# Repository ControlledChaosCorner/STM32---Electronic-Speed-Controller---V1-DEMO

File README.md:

# STM32---Electronic-Speed-Controller---V1-DEMO

The first version as a proof of concept and schematic verification for a simple brushed and brushless ESC. Based around an STM32, this will be an open source project starting point that will soon be replaced by a fully self contained, fully functional ESC. Files Designed for use in KiCad

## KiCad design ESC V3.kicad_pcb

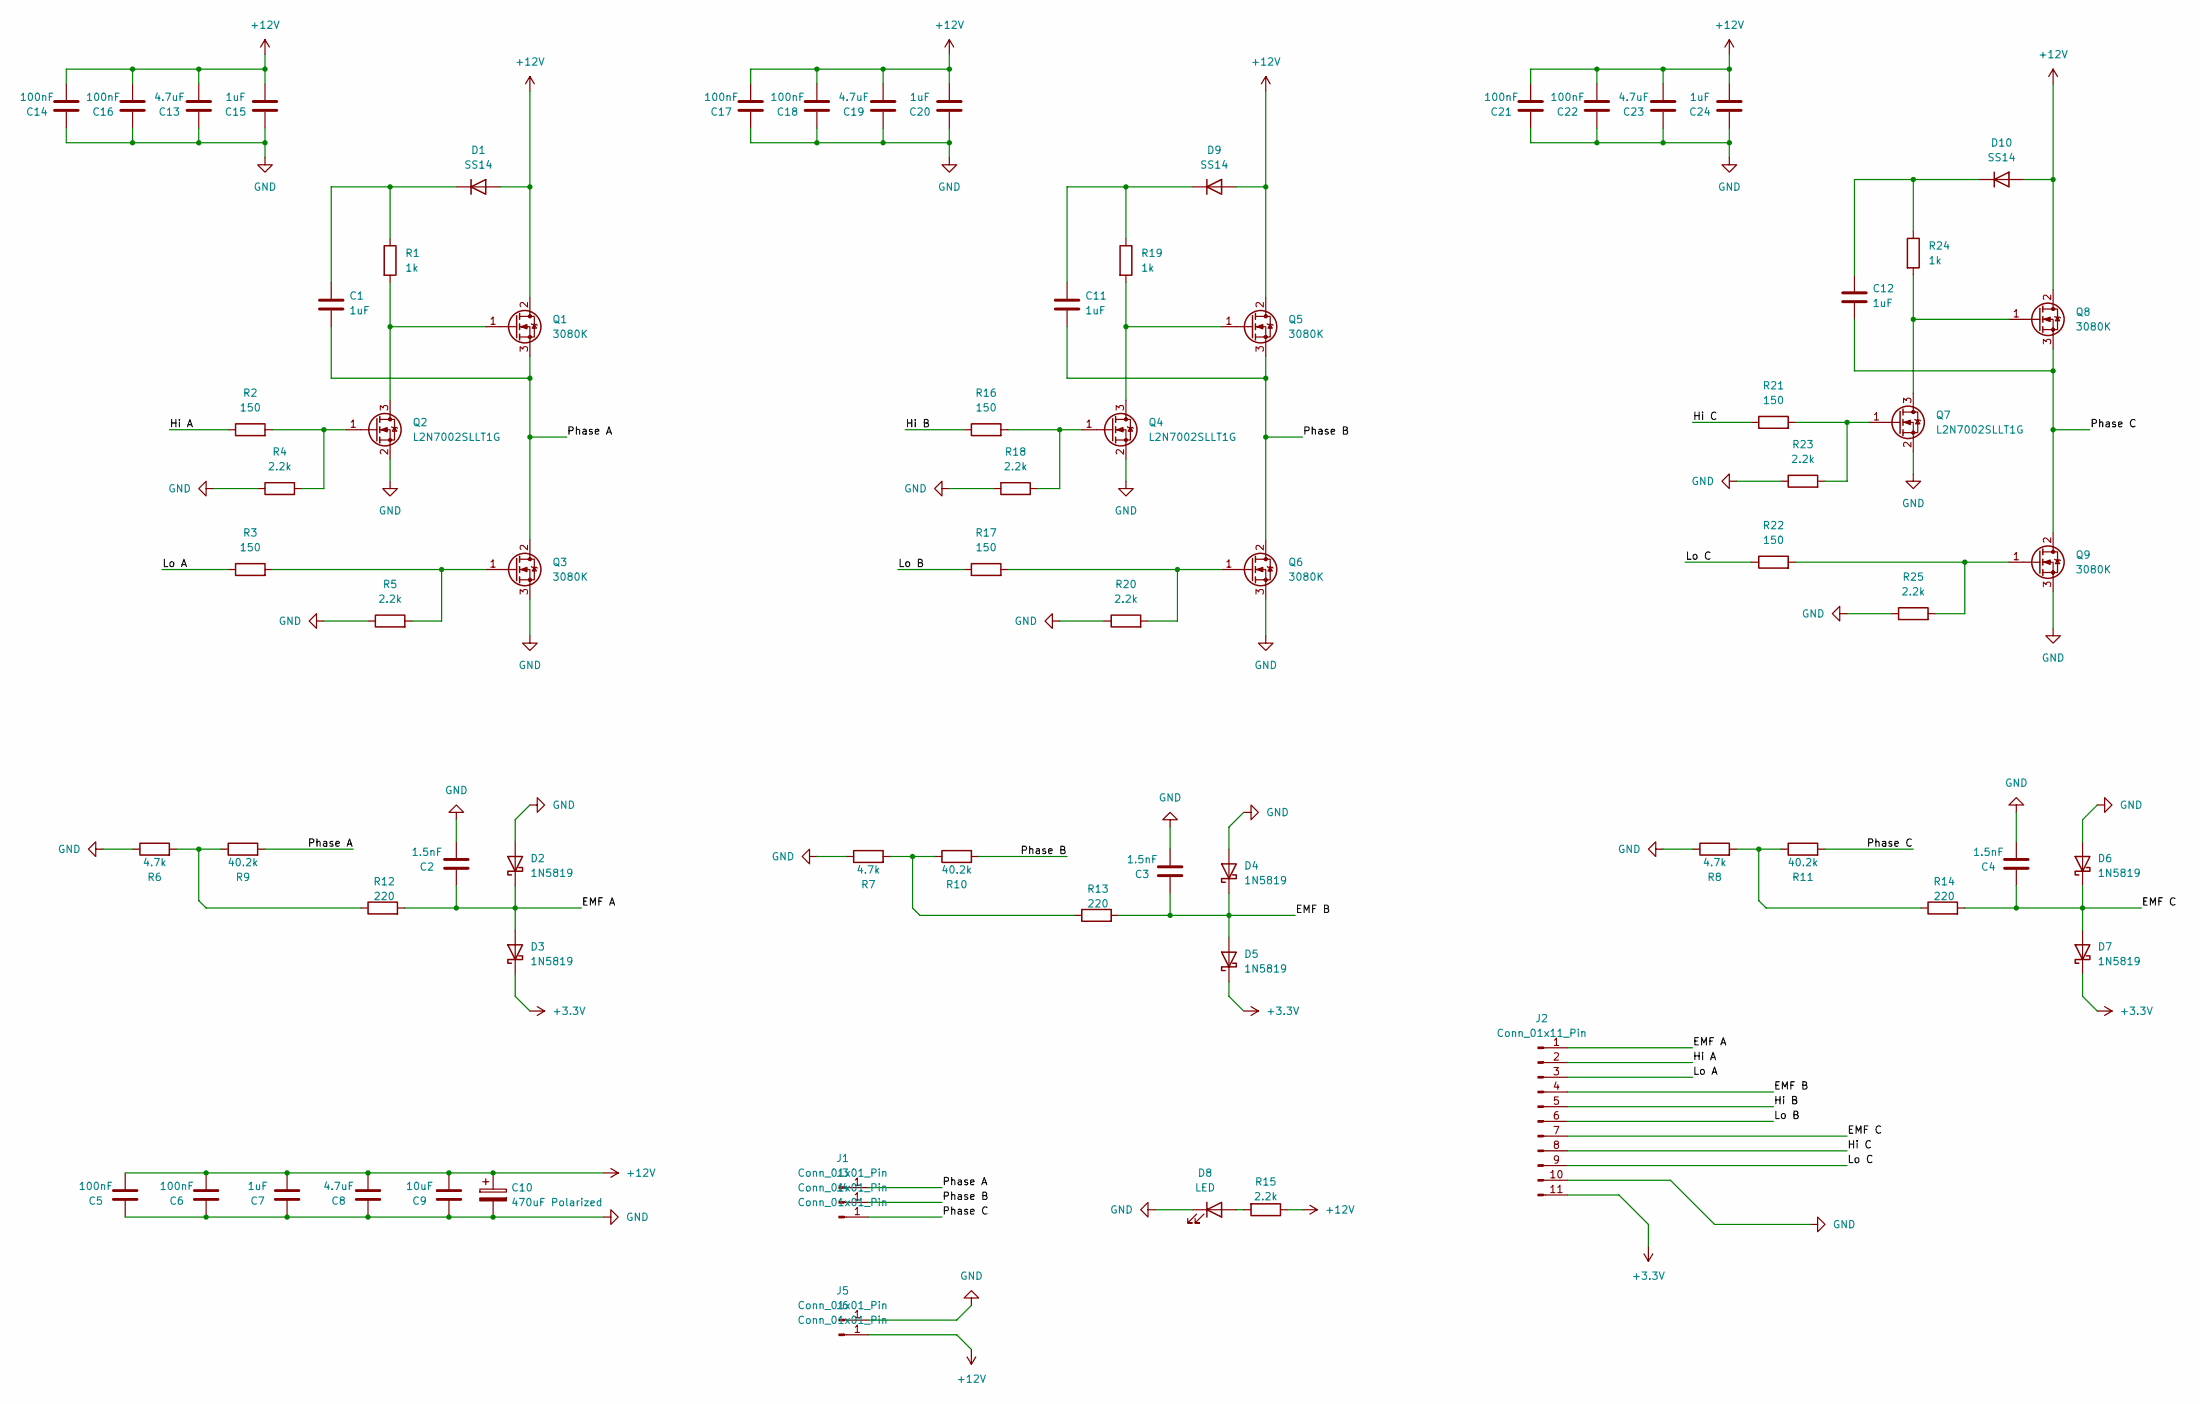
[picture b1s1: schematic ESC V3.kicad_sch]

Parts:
C1, C7, C11, C12, C15, C20, C24: 1uF; C_0603_1608Metric
C2, C3, C4: 1.5nF; C_0603_1608Metric
C5, C6, C14, C16, C17, C18, C21, C22: 100nF; C_0603_1608Metric
C8, C13, C19, C23: 4.7uF; C_0603_1608Metric
C9: 10uF; C_0805_2012Metric
C10: 470uF Polarized; CP_Radial_D10.0mm_P5.00mm
D1, D9, D10: SS14; D_SOD-128
D2, D3, D4, D5, D6, D7: 1N5819; D_SOD-123
D8: LED; LED_0603_1608Metric
J1, J3, J4, J5, J6: Conn_01x01_Pin; PinHeader_1x01_P2.54mm_Vertical
J2: Conn_01x11_Pin; PinHeader_1x11_P2.54mm_Vertical
Q1, Q3, Q5, Q6, Q8, Q9: 3080K; TO-252-2
Q2, Q4, Q7: L2N7002SLLT1G; SOT-23
R1, R19, R24: 1k; R_0603_1608Metric
R2, R3, R16, R17, R21, R22: 150; R_0603_1608Metric
R4, R5, R15, R18, R20, R23, R25: 2.2k; R_0603_1608Metric
R6, R7, R8: 4.7k; R_1206_3216Metric
R9, R10, R11: 40.2k; R_0805_2012Metric
R12, R13, R14: 220; R_0805_2012Metric

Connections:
+3.3V: D3.1 (K), D5.1 (K), D7.1 (K), J2.11
+12V: C5.2, C6.2, C7.2, C8.2, C9.2, C10.1, C13.2, C14.2, C15.2, C16.2, C17.2, C18.2, C19.2, C20.2, C21.2, C22.2, C23.2, C24.2, D1.2 (A), D9.2 (A), D10.2 (A), J6.1, Q1.2 (D), Q5.2 (D), Q8.2 (D), R15.1
/EMF A: C2.1, D2.1 (K), D3.2 (A), J2.1, R12.2
/EMF B: C3.1, D4.1 (K), D5.2 (A), J2.4, R13.2
/EMF C: C4.1, D6.1 (K), D7.2 (A), J2.7, R14.2
/Hi A: J2.2, R2.1
/Hi B: J2.5, R16.1
/Hi C: J2.8, R21.1
/Lo A: J2.3, R3.1
/Lo B: J2.6, R17.1
/Lo C: J2.9, R22.1
/Phase A: C1.2, J1.1, Q1.3 (S), Q3.2 (D), R9.2
/Phase B: C11.2, J3.1, Q5.3 (S), Q6.2 (D), R10.2
/Phase C: C12.2, J4.1, Q8.3 (S), Q9.2 (D), R11.2
GND: C2.2, C3.2, C4.2, C5.1, C6.1, C7.1, C8.1, C9.1, C10.2, C13.1, C14.1, C15.1, C16.1, C17.1, C18.1, C19.1, C20.1, C21.1, C22.1, C23.1, C24.1, D2.2 (A), D4.2 (A), D6.2 (A), D8.1 (K), J2.10, J5.1, Q2.2 (S), Q3.3 (S), Q4.2 (S), Q6.3 (S), Q7.2 (S), Q9.3 (S), R4.1, R5.1, R6.1, R7.1, R8.1, R18.1, R20.1, R23.1, R25.1
unnamed: C1.1, D1.1 (K), R1.1
unnamed: D8.2 (A), R15.2
unnamed: C11.1, D9.1 (K), R19.1
unnamed: C12.1, D10.1 (K), R24.1
unnamed: Q1.1 (G), Q2.3 (D), R1.2
unnamed: Q2.1 (G), R2.2, R4.2
unnamed: Q3.1 (G), R3.2, R5.2
unnamed: Q4.3 (D), Q5.1 (G), R19.2
unnamed: Q4.1 (G), R16.2, R18.2
unnamed: Q6.1 (G), R17.2, R20.2
unnamed: Q7.3 (D), Q8.1 (G), R24.2
unnamed: Q7.1 (G), R21.2, R23.2
unnamed: Q9.1 (G), R22.2, R25.2
unnamed: R7.2, R10.1, R13.1
unnamed: R8.2, R11.1, R14.1
unnamed: R6.2, R9.1, R12.1

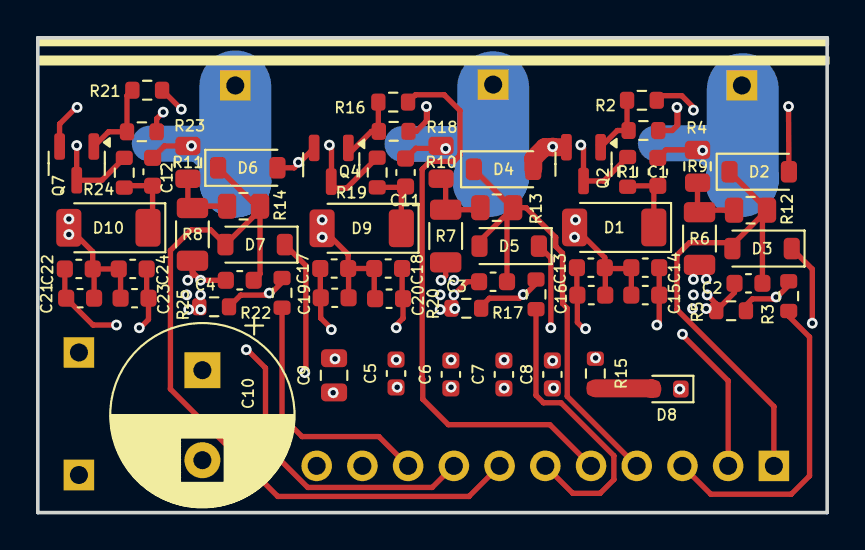
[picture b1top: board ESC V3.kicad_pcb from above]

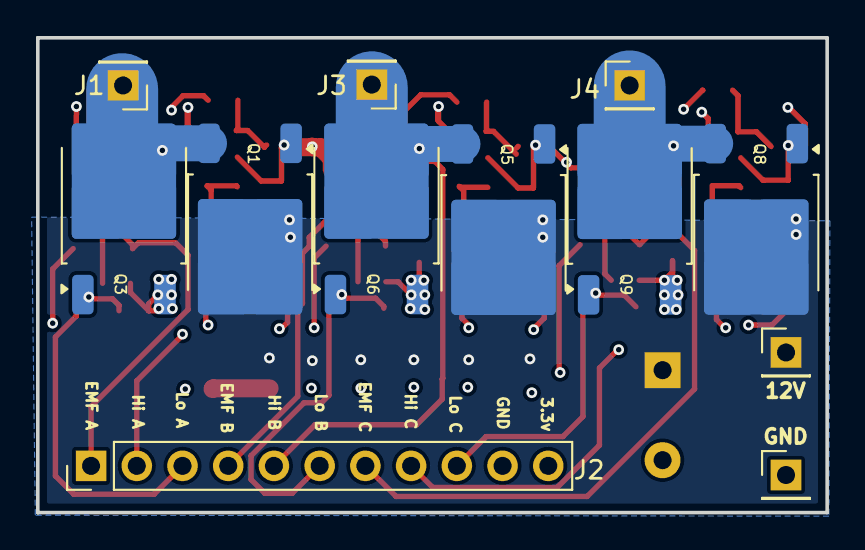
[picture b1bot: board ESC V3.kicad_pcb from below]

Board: 4 copper layers, 43.9 x 26.4 mm, 74 parts (12 on the bottom side), 31 nets.
